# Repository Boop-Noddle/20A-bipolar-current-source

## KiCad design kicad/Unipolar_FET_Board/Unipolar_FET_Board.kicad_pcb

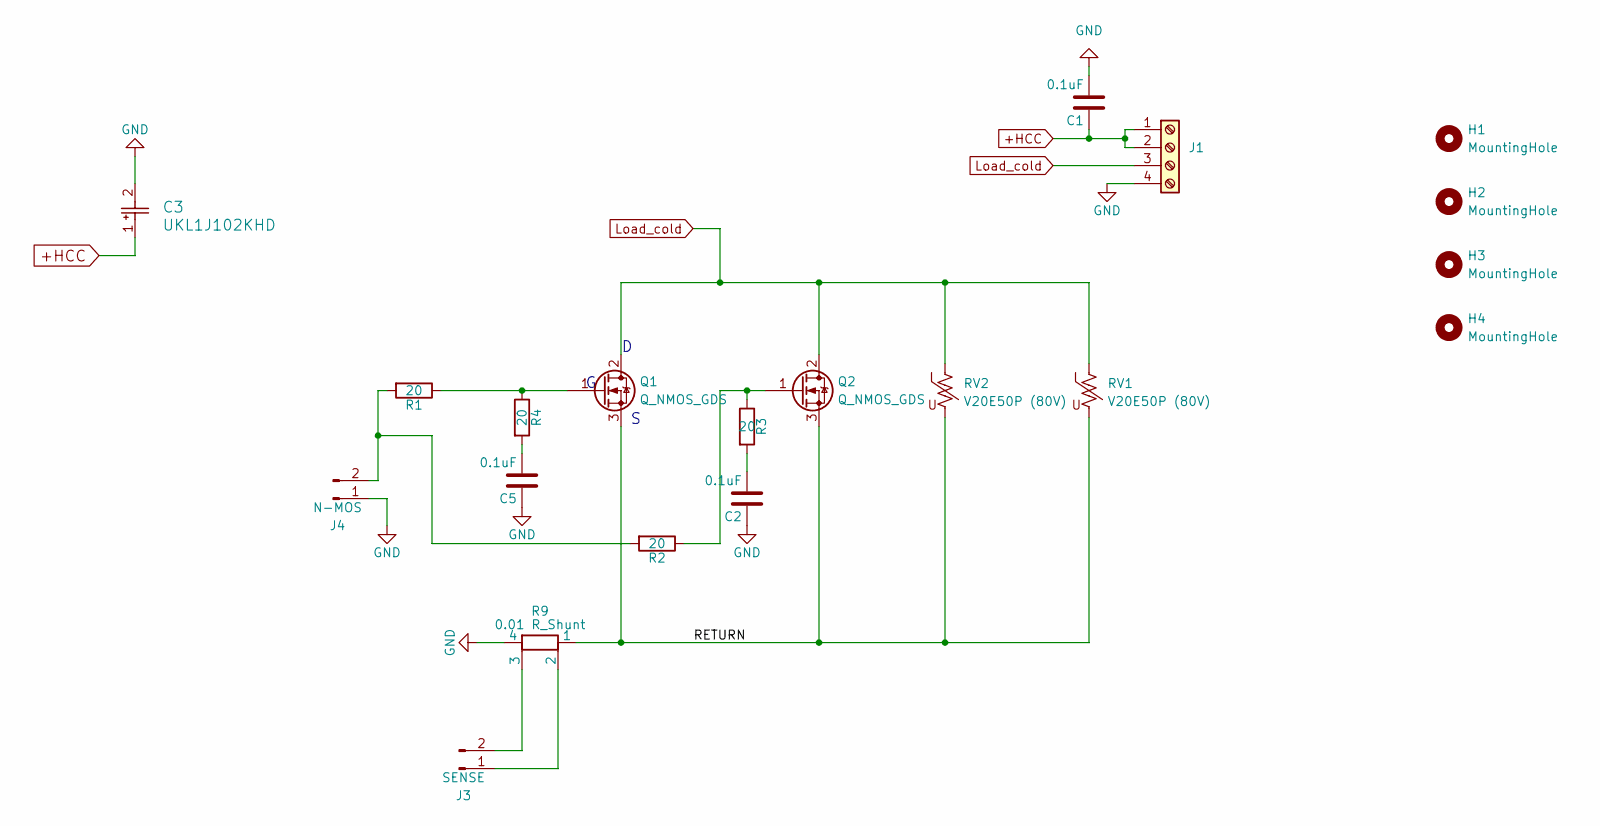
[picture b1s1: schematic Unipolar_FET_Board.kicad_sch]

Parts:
C1, C2, C5: 0.1uF; C_0603_1608Metric; MPN C0603C104J5RACAUTO; DIGIKEY PARTNO 399-6853-1-ND
C3: UKL1J102KHD; CP_Radial_D18.0mm_P7.50mm; PARTNO UKL1J102KHD; DIGIKEY 493-16867-ND
H1, H2, H3, H4: MountingHole; MountingHole_4mm
J1: Screw_Terminal_01x04; CONN_2453710000; PARTNO 2453710000; DIGIKEY 2453710000-ND
J3: SENSE; PinHeader_1x02_P2.54mm_Vertical
J4: N-MOS; PinHeader_1x02_P2.54mm_Vertical
Q1, Q2: Q_NMOS_GDS; PowerMOS; PARTNO IXFN520N075T2; DIGIKEY IXFN520N075T2-ND
R1, R2, R3, R4: 20; R_0603_1608Metric_Pad0.98x0.95mm_HandSolder; DIGIKEY PARTNO P20.00BYCT-ND
R9: 0.01 R_Shunt; SIP-4-ShuntResistor-Riedon; PARTNO PCS-0R01D1; DIGIKEY 696-PCS-0R01D1-ND
RV1, RV2: V20E50P (80V); RV_Disc_D15.5mm_W7.5mm_P7.5mm; PARTNO V20E50P; DIGIKEY F6901-ND

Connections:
+HCC: C1.1, C3.1, J1.1, J1.2
/RETURN: Q1.3 (S), Q2.3 (S), R9.1, RV1.2, RV2.2
GND: C1.2, C2.1, C3.2, C5.1, J1.4, J4.1, R9.4
Load_cold: J1.3, Q1.2 (D), Q2.2 (D), RV1.1, RV2.1
unnamed: C2.2, R3.2
unnamed: C5.2, R4.2
unnamed: J3.1, R9.2
unnamed: J3.2, R9.3
unnamed: J4.2, R1.2, R2.2
unnamed: Q1.1 (G), R1.1, R4.1
unnamed: Q2.1 (G), R2.1, R3.1

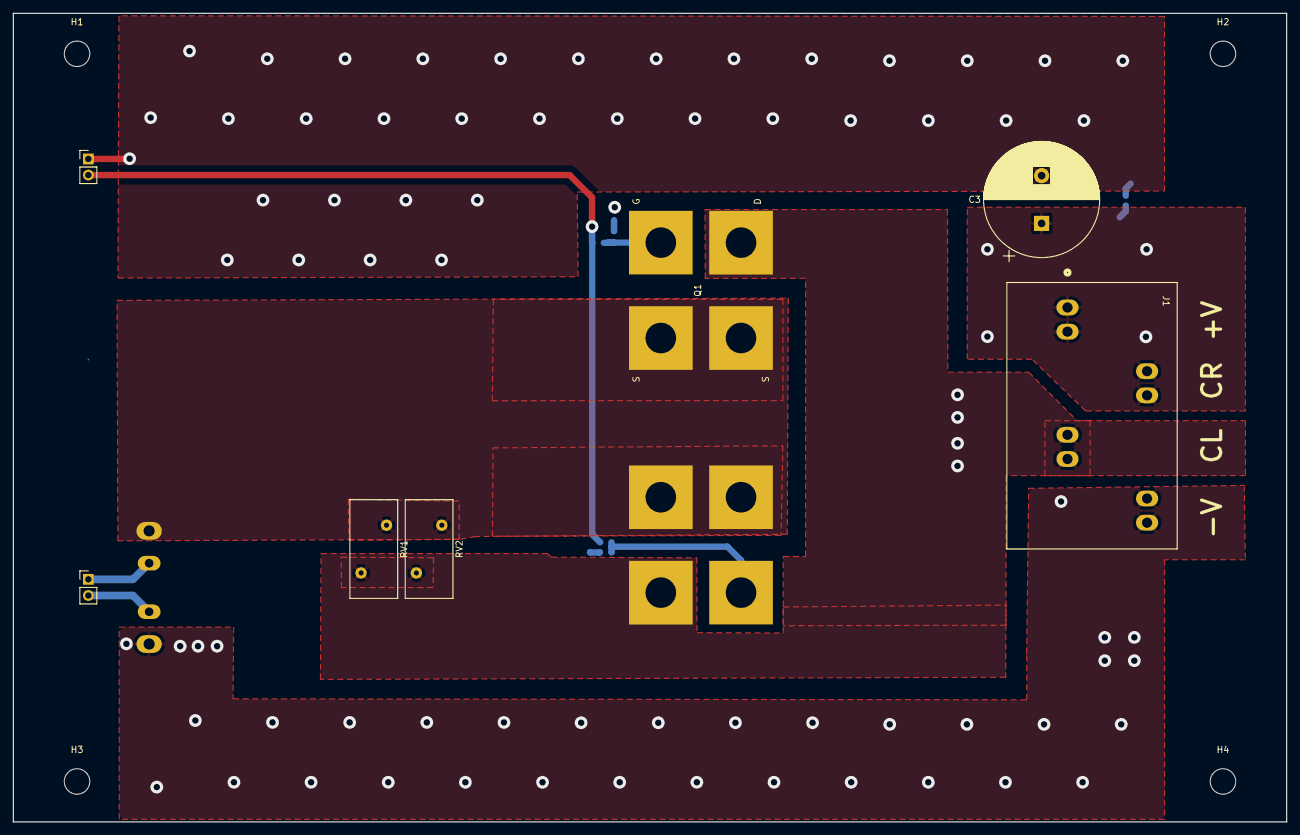
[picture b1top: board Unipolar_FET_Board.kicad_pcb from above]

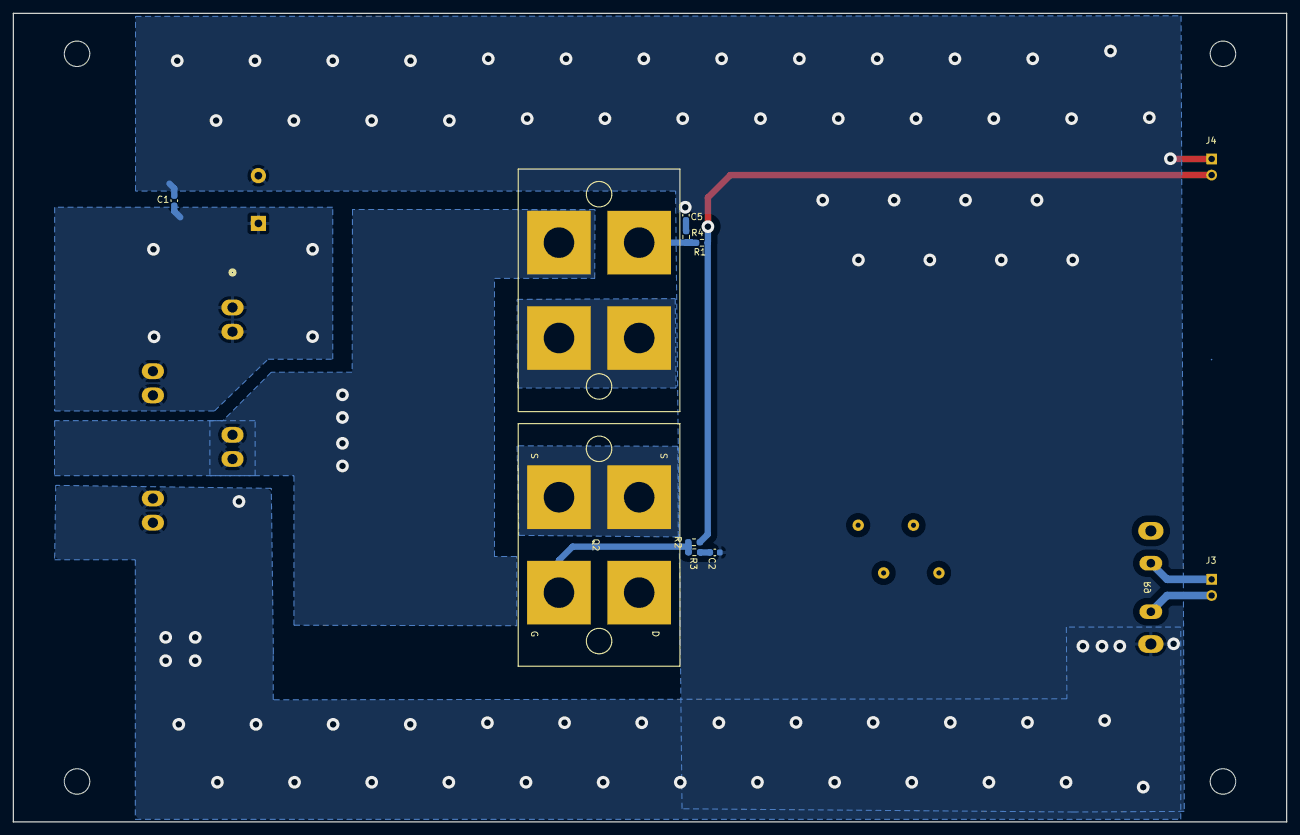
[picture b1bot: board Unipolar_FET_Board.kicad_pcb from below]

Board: 2 copper layers, 200.0 x 127.0 mm, 20 parts (9 on the bottom side), 11 nets.

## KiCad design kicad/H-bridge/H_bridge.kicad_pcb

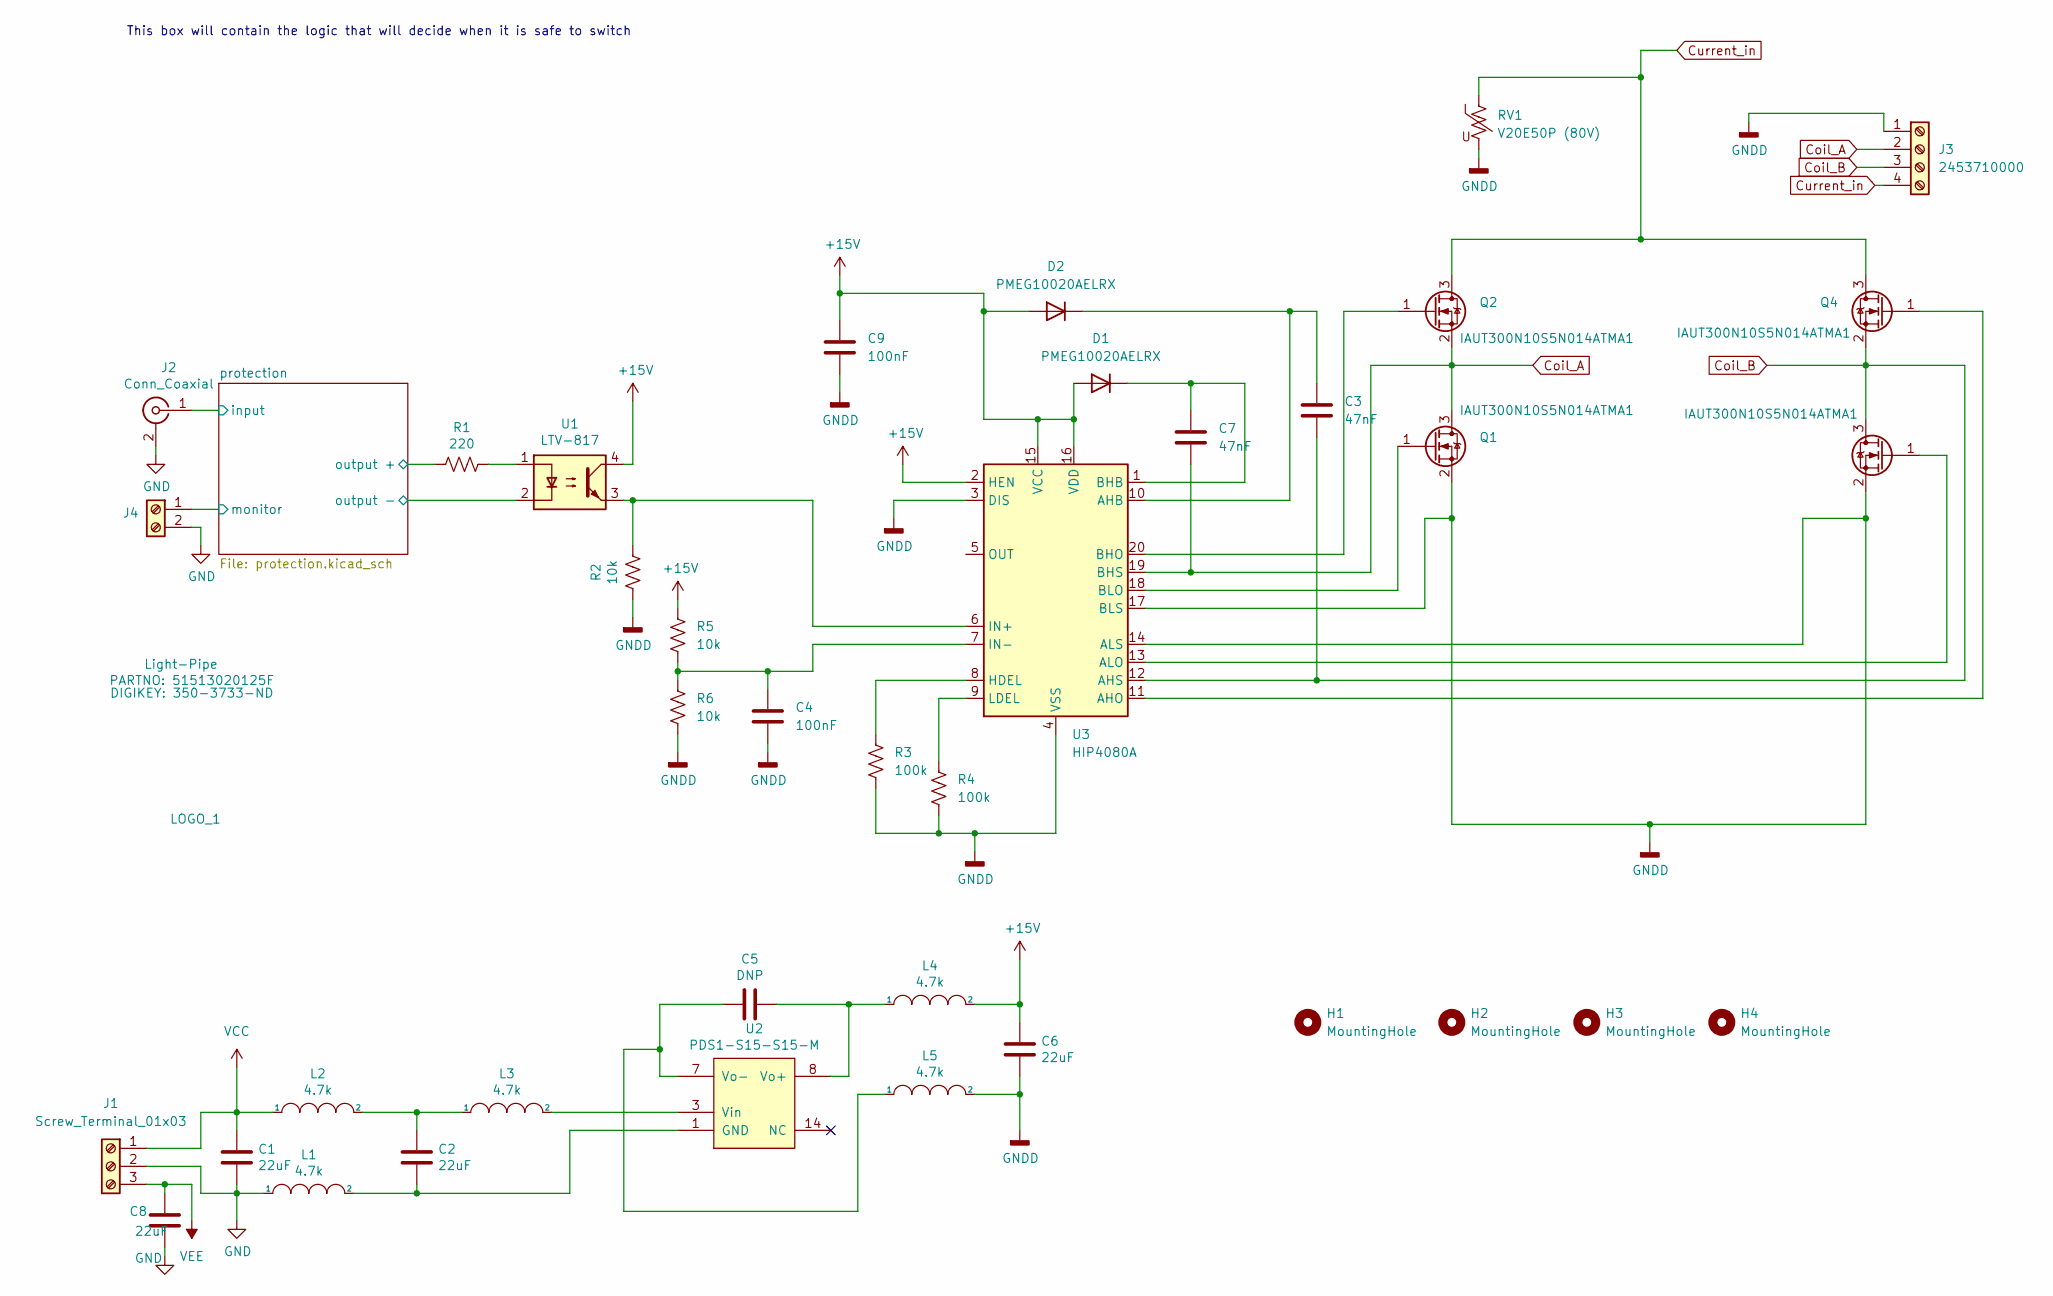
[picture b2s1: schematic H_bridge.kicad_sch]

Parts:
BOM1: Light-Pipe; PARTNO 51513020125F; DIGIKEY 350-3733-ND
C1, C2, C6, C8: 22uF; C_0805_2012Metric; PARTNO C2012X5R1V226M125AC; DIGIKEY 445-14428-1-ND
C3, C7: 47nF; C_0805_2012Metric; PARTNO C0805C473K2RECAUTO; DIGIKEY 399-C0805C473K2RECAUTOCT-ND
C4, C9: 100nF; C_0805_2012Metric; PARTNO CC0805KRX7R9BB104; DIGIKEY 311-1140-1-ND
C5: DNP; C_0805_2012Metric
D1, D2: PMEG10020AELRX; Nexperia_CFP3_SOD-123W; PARTNO PMEG10020AELRX; DIGIKEY 1727-2283-1-ND
H1, H2, H3, H4: MountingHole; MountingHole_3.5mm
J1: Screw_Terminal_01x03; TerminalBlock_4Ucon_1x03_P3.50mm_Horizontal; PARTNO 1984620; DIGIKEY 277-1722-ND
J2: Conn_Coaxial; BNC_Socket_TYCO-AMP; PARTNO 5227161-7; DIGIKEY A32260-ND
J3: 2453710000; CONN_2453710000; PARTNO 2453710000; DIGIKEY 2453710000-ND
J4: Screw_Terminal_01x02; TerminalBlock_4Ucon_1x02_P3.50mm_Horizontal; PARTNO 1984617; DIGIKEY 277-1721-ND
L1, L2, L3, L4, L5: 4.7k; L_0805; PARTNO BLM21HE472SN1L; DIGIKEY 490-BLM21HE472SN1LCT-ND
LOGO_1: JQI-Logo
Q1, Q2, Q3, Q4: IAUT300N10S5N014ATMA1; Infineon_PG-HSOF-8-1_ThermalVias; PARTNO IAUT300N10S5N014ATMA1; DIGIKEY 448-IAUT300N10S5N014ATMA1CT-ND
R1: 220; R_0805; PARTNO CRGCQ0805F220R; DIGIKEY A129741CT-ND
R2, R5, R6: 10k; R_0805_2012Metric; PARTNO CRGCQ0805F10K; DIGIKEY A129761CT-ND
R3, R4: 100k; R_0805_2012Metric; PARTNO CRG0805F100K; DIGIKEY A106052CT-ND
RV1: V20E50P (80V); RV_Disc_D15.5mm_W7.5mm_P7.5mm; PARTNO V20E50P; DIGIKEY F6901-ND
U1: LTV-817; DIP-4_W10.16mm_LongPads; PARTNO LTV-817; DIGIKEY 160-1366-5-ND
U2: PDS1-S15-S15-M; DCDC-Conv_muRata_NXE2SxxxxMC; PARTNO PDS1-S15-S15-M; DIGIKEY 102-4546-ND
U3: HIP4080A; SO-20_12.8x7.5mm_P1.27mm; PARTNO HIP4080AIBZT; DIGIKEY HIP4080AIBZTCT-ND

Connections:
+15V: C6.2, C9.1, D1.2 (A), D2.2 (A), L4.2, R5.1, U1.4, U3.2 (HEN), U3.15 (VCC), U3.16 (VDD)
/protection/input: J2.1 (In); also elsewhere on the board
/protection/monitor: J4.1; also elsewhere on the board
/protection/output +: R1.2; also elsewhere on the board
/protection/output -: U1.2; also elsewhere on the board
Coil_A: C7.2, J3.2, Q1.3 (D), Q2.2 (S), U3.19 (BHS)
Coil_B: C3.2, J3.3, Q3.3 (D), Q4.2 (S), U3.12 (AHS)
Current_in: J3.4, Q2.3 (D), Q4.3 (D), RV1.1
GND: C1.2, C8.2, J1.2, J2.2 (Ext), J4.2, L1.1; also elsewhere on the board
GNDD: C4.2, C6.1, C9.2, J3.1, L5.2, Q1.2 (S), Q3.2 (S), R2.2, R3.2, R4.2, R6.2, RV1.2, U3.3 (DIS), U3.4 (VSS), U3.14 (ALS), U3.17 (BLS)
unnamed: C2.1, L2.2, L3.1
unnamed: C7.1, D1.1 (K), U3.1 (BHB)
unnamed: C3.1, D2.1 (K), U3.10 (AHB)
unnamed: Q1.1 (G), U3.18 (BLO)
unnamed: Q2.1 (G), U3.20 (BHO)
unnamed: Q3.1 (G), U3.13 (ALO)
unnamed: Q4.1 (G), U3.11 (AHO)
unnamed: R1.1, U1.1
unnamed: C2.2, L1.2, U2.1 (GND)
unnamed: L3.2, U2.3 (Vin)
unnamed: C5.1, L4.1, U2.8 (Vo+)
unnamed: C5.2, L5.1, U2.7 (Vo-)
unnamed: R3.1, U3.8 (HDEL)
unnamed: R2.1, U1.3, U3.6 (IN+)
unnamed: C4.1, R5.2, R6.1, U3.7 (IN-)
unnamed: R4.1, U3.9 (LDEL)
VEE: C8.1, J1.3; also elsewhere on the board

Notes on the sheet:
This box will contain the logic that will decide when it is safe to switch

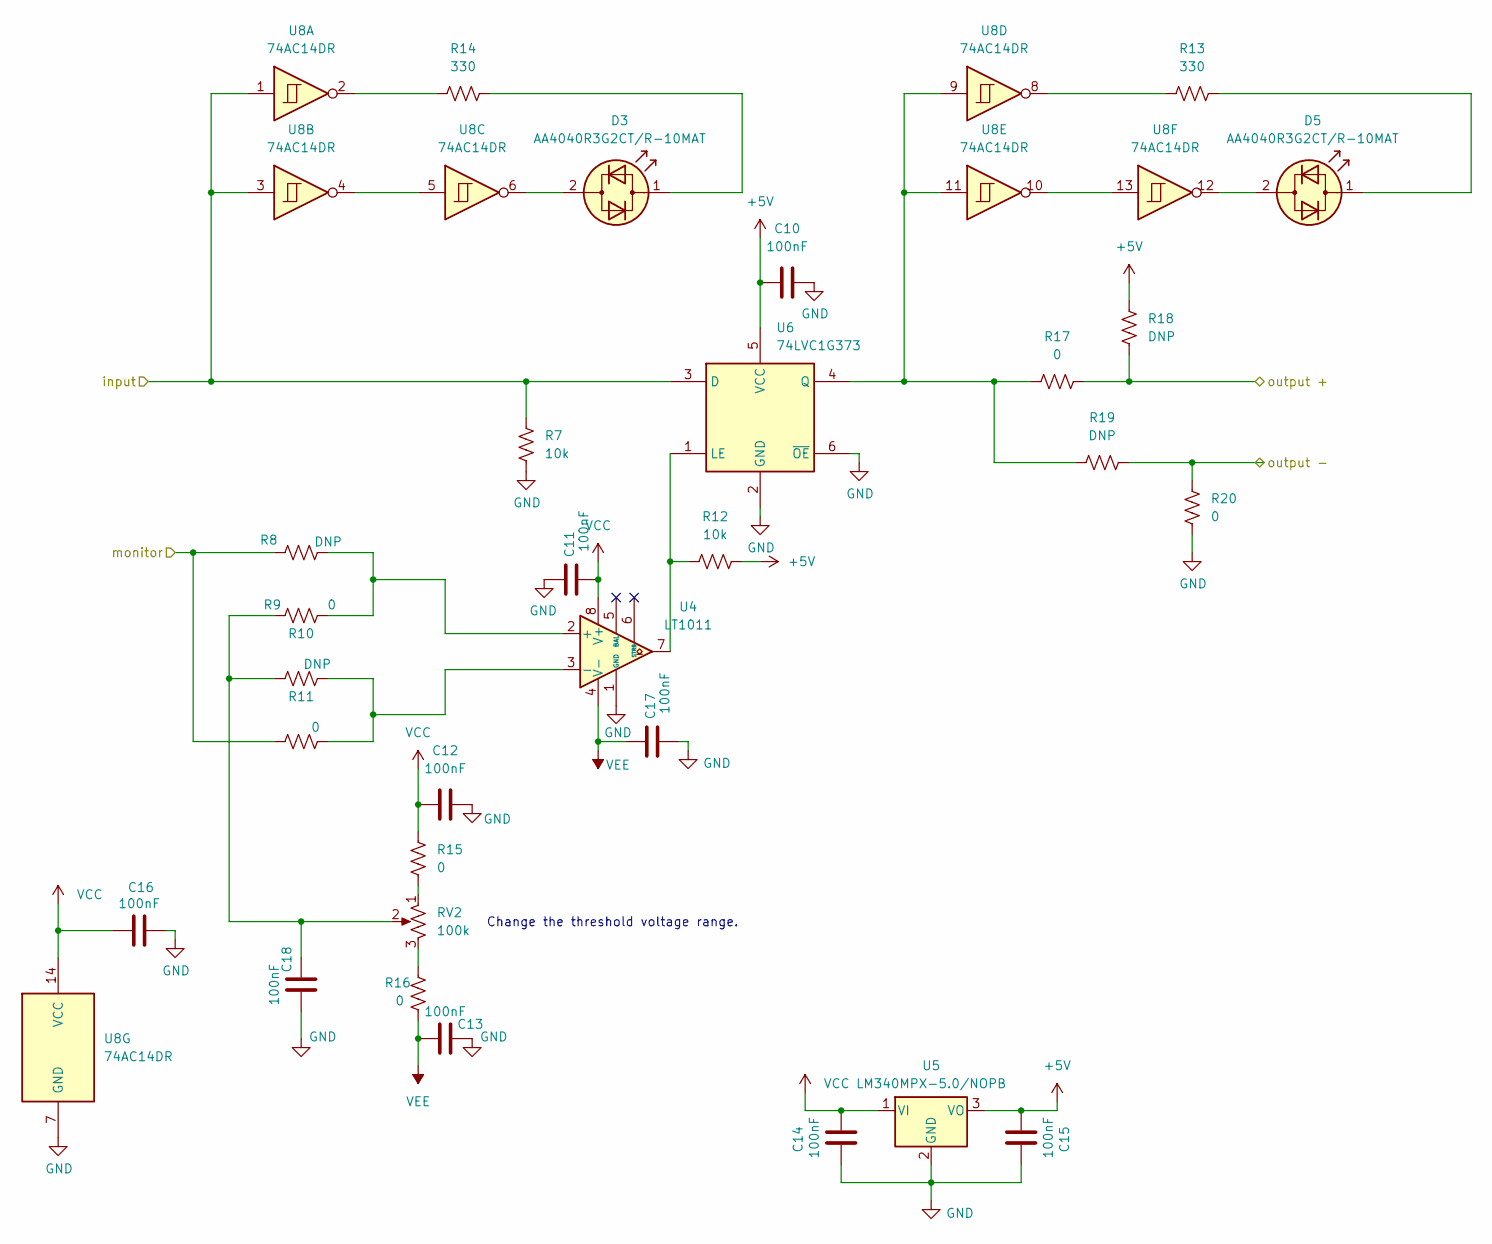
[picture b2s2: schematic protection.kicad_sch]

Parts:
C10, C11, C12, C13, C14, C15, C16, C17, C18: 100nF; C_0805_2012Metric; PARTNO CC0805KRX7R9BB104; DIGIKEY 311-1140-1-ND
D3, D5: AA4040R3G2CT/R-10MAT; LED_boomerang; PARTNO AA4040R3G2CT/R-10MAT; DIGIKEY 754-AA4040R3G2CT/R-10MATCT-ND
R7, R12: 10k; R_0805_2012Metric; PARTNO CRGCQ0805F10K; DIGIKEY A129761CT-ND
R8, R10, R18, R19: DNP; R_0805_2012Metric
R9, R11, R15, R16, R17, R20: 0; R_0805_2012Metric; PARTNO CRG0805ZR; DIGIKEY A106066CT-ND
R13, R14: 330; R_0805_2012Metric; PARTNO CRGCQ0805F330R; DIGIKEY A129743CT-ND
RV2: 100k; Potentiometer_Bourns_3266Y_Vertical; PARTNO 3266Y-1-104LF; DIGIKEY 3266Y-1-104LF-ND
U4: LT1011; SO-8_3.9x4.9mm_P1.27mm; PARTNO LT1011CS8#PBF; DIGIKEY LT1011CS8#PBF-ND
U5: LM340MPX-5.0/NOPB; SOT-223-3_TabPin2; PARTNO LM340MPX-5.0/NOPB; DIGIKEY LM340MPX-5.0/NOPBCT-ND
U6: 74LVC1G373; SOT-363_SC-70-6; PARTNO SN74LVC1G373DCKR; DIGIKEY 296-18775-1-ND
U8: 74AC14DR; SOIC-14_3.9x8.7mm_P1.27mm; PARTNO SN74AC14DR; DIGIKEY 296-4300-1-ND

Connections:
/protection/input: R7.1, U6.3 (D), U8.1, U8.3; also elsewhere on the board
/protection/monitor: R8.1, R11.1; also elsewhere on the board
/protection/output +: R17.2, R18.1; also elsewhere on the board
/protection/output -: R19.1, R20.2; also elsewhere on the board
GND: C10.2, C11.2, C12.2, C13.2, C14.1, C15.1, C16.1, C17.1, C18.1, R7.2, R20.1, U4.1 (GND), U5.2 (GND), U6.2 (GND), U6.6 (~OE), U8.7 (GND); also elsewhere on the board
unnamed: C18.2, R9.1, R10.1, RV2.2
unnamed: D3.2 (AK), U8.6
unnamed: D3.1 (KA), R14.2
unnamed: D5.2 (AK), U8.12
unnamed: D5.1 (KA), R13.2
unnamed: R13.1, U8.8
unnamed: R14.1, U8.2
unnamed: R15.1, RV2.1
unnamed: R16.2, RV2.3
unnamed: R8.2, R9.2, U4.2 (+)
unnamed: R10.2, R11.2, U4.3 (-)
unnamed: R12.1, U4.7, U6.1 (LE)
unnamed: R17.1, R19.2, U6.4 (Q), U8.9, U8.11
unnamed: U8.4, U8.5
unnamed: U8.10, U8.13
VEE: C13.1, C17.2, R16.1, U4.4 (V-); also elsewhere on the board

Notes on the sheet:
Change the threshold voltage range.

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
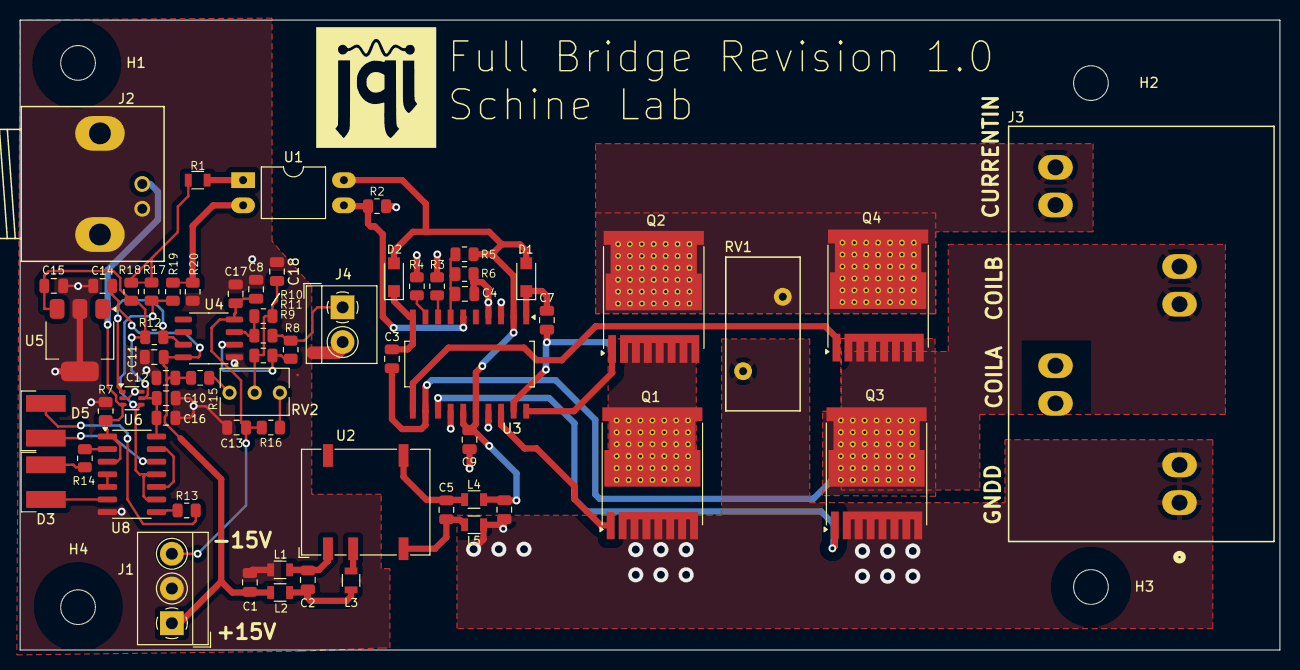
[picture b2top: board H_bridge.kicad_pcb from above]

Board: 2 copper layers, 127.0 x 63.5 mm, 69 parts (0 on the bottom side), 44 nets.

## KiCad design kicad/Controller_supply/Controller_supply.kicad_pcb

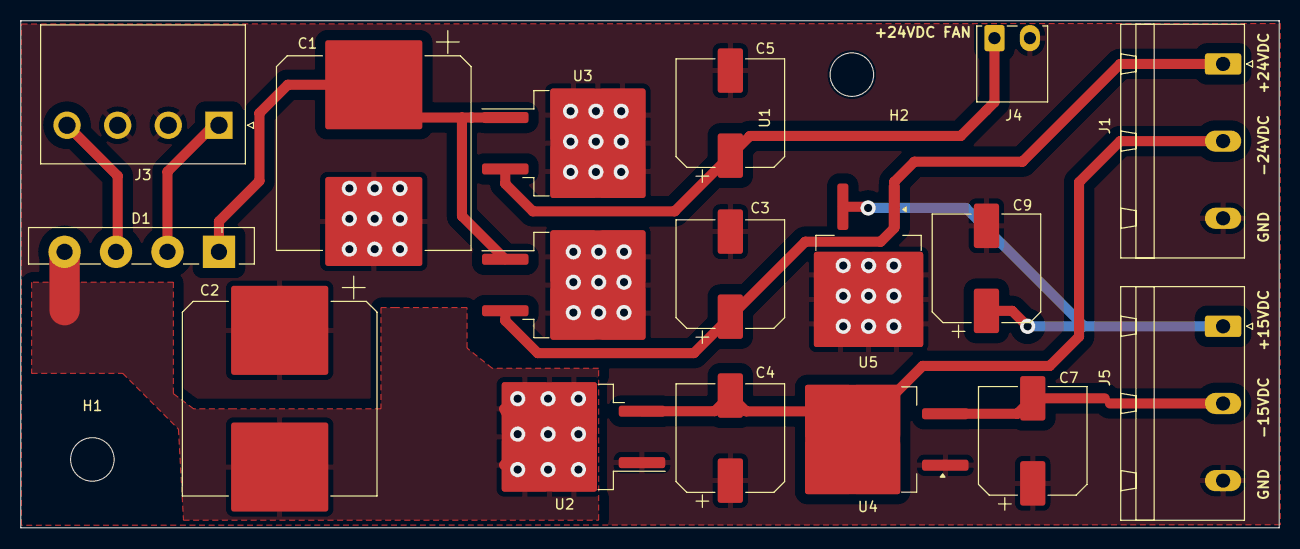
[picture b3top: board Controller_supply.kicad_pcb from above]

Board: 2 copper layers, 124.3 x 50.1 mm, 19 parts (0 on the bottom side), 10 nets.

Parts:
C1, C2: 3000uF; CP_Elec_18x22
C3, C4, C5, C7, C9: 220uF; CP_Elec_10x10.5
D1: GBU4A; Diode_Bridge_Vishay_GBU
H1, H2: MountingHole_4.3mm_M4
J1, J5: Conn_01x03_Pin; PhoenixContact_GMSTBA_2,5_3-G-7,62_1x03_P7.62mm_Horizontal
J3: Conn_01x04_Pin; Generic_pin-to-housing_1x04_P5.00mm_Horizontal
J4: Conn_01x02; Generic_7x7.5mm-footprt_1x02_P3.50mm_Horizontal
U1, U3: MC7824; TO-263-2
U2: MC7924; TO-263-2
U4: MC7915; TO-263-2
U5: L7815; TO-263-2

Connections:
+15VDC: C9.1, J5.1, U5.3 (OUT)
+24AC: D1.3, J3.4
+24VDC: C3.1, J1.1, U1.3 (OUT), U5.1 (IN)
+24VDC_fan: C5.1, J4.1, U3.3 (OUT)
-15VDC: C7.2, J5.2, U4.3 (VO)
-24AC: D1.2, J3.1
-24VDC: C4.2, J1.2, U2.3 (VO), U4.2 (VI)
GND: C1.2, C2.1, C3.2, C4.1, C5.2, C7.1, C9.2, J1.3, J3.2, J3.3, J4.2, J5.3, U1.2 (GND), U2.1 (GND), U3.2 (GND), U4.1 (GND), U5.2 (GND)
unnamed: C1.1, D1.1 (+), U1.1 (IN), U3.1 (IN)
unnamed: C2.2, D1.4 (-), U2.2 (VI)

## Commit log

2024-05-27 First iteration of the layout
2024-06-06 2nd iteration
2024-06-12 H_bridge circuit with current control ciruit added
2024-06-14 Fixed silkscreen placement
2024-06-14 Added sub-circuit
2024-06-18 Added C18, logo and other footprints
2024-06-19 Fixed error is MOS package assigment and added solder mask for manual tin pour for increased conductivity
2024-06-24 fixed connection error and added text
2024-06-28 Aligned mountiing holes
2024-07-11 Unipolar Fet Board v1.0
2024-07-11 Added vias'
2024-07-11 Added varistor and labesl for the connecters
2024-07-12 Parallel MOS with current sharing resistors
    Putting additional resistors in series with the source of each MOS is not necessary.
    Nonetheless I saved this partiular snapshot in case we want to pursuit this strategy to share the current
2024-07-26 15V output modification
2024-07-26 Trimportand INverter power supply fix, now connects to 5V
2024-07-26 Added silkscreen
2024-07-29 The MOS and capacitors are now in the correct orientation
2024-07-29 Seperated zones
2025-05-27 Addtional Testing Data and reports
